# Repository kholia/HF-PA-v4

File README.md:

### HF-PA-v4

VU3CER's Robust `Class-D HF PA` for https://github.com/kholia/Easy-Digital-Beacons-v1
project for 40-20-17-15-10 bands.

For extra fun, use this PA with https://github.com/kholia/HF-Balcony-Antenna-System.

Jan-2022 UPDATE: https://github.com/kholia/HF-PA-v5 is up now.

This design aspires to be the standard mW-to-QRP-Gallon HF PA in the ~600 INR
(8 USD) design space. Well, it does much more than QRP now...

Design Constraints:

- PCB is to be homebrewed.

- PCB is single-sided - only one layer (side) is available for routing.

- IRF510 MOSFET needs to be on an edge to allow usage of heatsinks.

- Typical external linears (e.g. `PA150 HF Linear Amp`) need 2W minimum to
  function. So we need a minimum of 2W of RF output from our design.

- Minimal part count is strongly preferred. Low cost, and ease of availability
  are strong driving and deciding factors.

  The cost of this HF-PA-v4 system is less than one RD16HHF1 MOSFET ;)

- Reproducibility is a MUST! We focus a lot on this aspect by documenting each,
  and every detail possible.

- Repairability in the field is a MUST!

  Dhiru's finding: Repairing homebrewed PCBs is so much easier, and fun than
  reworking commercial `lead-free` PTH PCBs.

- No moving mechanical parts are allowed in the design - this rules out usage
  of (failure-prone) active cooling options like fans.

- We do NOT like the robustness of QCX, QDX, uSDX PAs. Removing heat from TO-92
  devices in a reliable way is not a trivial problem.

Note 0: All screenshots are clickable and zoomable.

Input: Few milliwatts is fine. Note: Si5351's output is around 8-10mW.

Output: With `v4.1` design, we are able to get 12W+ (total power) on the 15m
band with 30% efficiency! With a 5-pole LPF attached, we get ~10W RF output on
the 15m band. Efficiencies and output power levels are much higher on lower
bands! E.g. Power output @ 14 MHz is 14W+ with 51% efficiency - with LPF
attached!

Old results (kept for reference purposes):

Sample output for (14 MHz, 20v, ~725mA IN, 15W DC IN, 5.2W RF OUTPUT, With LPF
attached):

Note 1: The output power is software controllable (via `PWM grounding`) for
flexibility.

Note 2: The idea behind making these (and my other) design notes publicly
available is to deliver REPRODUCIBLE, flexible, home-brewable, standardized,
reasonable, and cost-effective solutions for some common problems. I include
many references, simulations, and notes in my projects to enable you to do your
own (better) designs - do share them ;)

Robustness Notes:

- Ensure that the IRF510 is fastened securely to the heat sink.

  Use lock washers, and thermal epoxy adhesive to ensure good mechanical
  contact.

- We recommend operating at 24v instead of >= 29v.

**Final recommendations from 05-November-2021 (for v4.3)**:

- Using 7805 is recommended instead of 7809 / 7912. Less is more ;)

- Enable `SI5351_DRIVE_8MA` option in code.

- Output results @ 24v:

  - 28.075 MHz (10m): 4W RF OUT (~14.5W DC IN)

  - 21.075 MHz (15m): 5W RF OUT (~13W DC IN)

  - 14.075 MHz (20m): 7W RF OUT (~13W DC IN)

For more power, use 7809 instead of 7805, and remember to take (much) more
care!

Please see the older https://github.com/kholia/HF-PA-v2 project for the
power-supply (over-current protected), and LPF designs.

Schematic:

PCB rendering (v4.1):

Note 3: The HF PA is connected to a 20m dipole over 55 meters of HLF-200 coax.

Note 4: The PCB is done using KiCad - a free, and open EDA software.

Note 5: This PA can be homebrewed from scratch in around 4 to 6 hours (one
afternoon, and an evening).

#### Notes

[From QRP Labs] Si5351A outputs a 3.3v square wave. The power output of Si5351A
is around 8-10mW (10 dBm). The BS170 based driver circuit amplifies this to
~200mW (23 dBm) for a gain of around 13 dB. The IRF510 finals provide a gain of
around 14dB and produce around 5W of RF power.

#### PA tuning process

- Remove the BS170 and IRF510 MOSFETS from their sockets.

- Set DC gate bias for BS170 to 0v. Now increase the bias (via trimpot) until
  the current consumption increases slightly (QRP Labs' process).

  You can also start by setting the gate bias to 2v directly ;)

- For IRF510, set gate bias to 3v. This ensures that IRF510 isn't turned ON -
  double-check this by monitoring the power consumption.

- Connect the MOSFET back, and measure RF output. Happy with the output power? -
  If yes, you are done else follow the next steps.

- Remove the MOSFET, increase the gate bias voltage in very small increments
  (0.1v types).

- Connect the MOSFET back, and measure power consumption without any RF input.
  Ensure that MOSFET remains OFF without any RF input.

- Apply RF input, and measure RF output.

- Repeat these steps as needed.

The [QRP Labs' procedure for bias adjustment](https://www.qrp-labs.com/images/pa/pa_simple_assembly_A4.pdf) and [this document](https://www.qrp-labs.com/images/ultimate3s/assembly_u3s.pdf) seem to have a better description of this process.

#### PA BOM

- 1 x IRF510 (Genuine Vishay parts are tried-and-tested) - 35 to 50 INR

  - The `SEC` (`SEC Electronics Inc`) branded IRF510(s) also work great!

  - The `SEC IRF510` can perform even better than Vishay's version. This
    particular result will vary between different product batches.

  - IRF510 with `International Rectifier` branding are most likely fake or "new
    old stock" if you are very lucky!

    Note: IR and Infineon have stopped manufacturing IRF510 MOSFETs.

  - AliExpress IRF510(s) are likely to be fake

  - The IR IRF510 gave ~3W versus 5.2W+ from SEC IRF510 versus ~5W from
    Vishay's IRF510!

    Note: The gate threshold voltage can vary even between two samples picked
    from the same manufacturer!

  - The Cgs ("gate capacitance") of a fake IRF510 is typically more than 1000pF
    on a LCR-T4 meter. This value is around ~400pF for genuine IRF510 parts on
    a LCR-T4 meter.

  - Ensure proper sourcing (trusted supply chain, etc) to get genuine parts

- BS170 MOSFET - 9 to 15 INR

- 2 x 4.7k Preset (Potentiometer) RM-065 - 12 INR

  - It is easier to get 5k (502) trimpots

- 1 x 3.3k 0.25W MFR - 2 INR

- 1 x 4.7k 0.25W MFR - 2 INR

- 1 x 10 Ohm Resistor 0.25W or 0.5W MFR - 2 INR (MOSFET gate resistor)

- [Optional] 2 x 10k Ohm - 0.25W Metal Film Resistor - 5 INR

- A very large heat sink - 50 to 175 INR - larger heatsink is better!

- 1 x 7805 (TO-220 package from CDIL) Voltage Regulator - 30 INR

  - The ST's 7805 is widely faked - let's avoid it or let's source it properly

- 1 x 1N4001 (or 1N4007) diode for 7805 protection - 2 INR

- 2 x SMA connectors (Vertical PCB mount) - 75 INR

- 1 x 10uF 50v Electrolytic Capacitor - 5 INR

- 8 x 100nF (104) 50v MLCC - 20 INR

- 1 x FT37-43 (Black Toroid, Fair-Rite 5943000201) - less than 25 INR (handles <= 350mW only)

- 1 x FT50-43 (Larger Black Toroid, Fair-Rite 5943000301) - less than 32 INR

- Misc: Relimate Connectors, Copper Clad PCB (Glass Epoxy), Various Consumables
  (~100 INR), SMA cables for testing, RF adapter (SMA Male to SO-239), M3 nuts
  and screws, TO-220 insulator kit

- Tools: LCR-T4 Meter (for measuring things), RF Power Meter

- Optional power supply: LM50-20B24 Mornsun SMPS - 24V 2.2A - 52.8W AC/DC SMPS - 700 INR

- Optional PPTC fuse

- PA Total Cost: Less than 600 INR

#### Power Supply + LPF BOM

See the following projects:

- https://github.com/kholia/HF-PA-v2
- https://github.com/kholia/HF-PA-v3
- 2 x 100 pF (50/100v)
- 1 x 180 pF (50/100v)
- 2 x T50-6 (Yellow Iron Dust code) toroids
- 25 SWG Winding Wire

Note: For LPF, use C0G 100v rated caps!

#### BOM + Equipment Sources

- https://www.semikart.com/ (IRF510, BS170, 100v NP0 LPF caps - Kemet and others)

  - 100v NP0 LPF caps from `Multicomp Pro` brand seem pretty cost-effective

  - 1N5374B 75V 5W Zener Diode (optional - for SWR protection)

- https://www.electronicscomp.com/

  - IRF510, BS170, regular caps, ST voltage regulators

  - Female berg strip (2.54mm pitch)

- https://www.electroncomponents.com/ (transistors, connectors, consumables, misc)

  - https://www.electroncomponents.com/LM7805-5V-Positive-Regulator

  - https://www.electroncomponents.com/BS170-N-channel-Switching-FET

  - https://www.electroncomponents.com/1N4001

  - https://www.electroncomponents.com/mica-insulator-to-220-set-kit

- https://www.sunrom.com/ (regular ceramic caps, SMA connectors)

- https://projectpoint.in/

  - Transistors, regular caps, voltage regulators, pots / trimmers, MFR resistors, misc

  - 2-Pin High Quality Relimate Connectors (all those 2-pin headers are actually Relimate Connectors)

  - Copper Magnetic Winding Wire - 29 SWG and 25 SWG

  - CDIL 7805

  - 3-Pin Relimate Cable Female to Female (High Quality 2500mA) - 'TO-220 socket'

  - 2-Pin Relimate Cable Female (High Quality 2500mA) - for power

  - 2-Pin Relimate Male Header

- Semikart, eBay (`gr_makis`) - Toroids

- https://www.onlinetps.com/shop/ ('IR branded' IRF510 - not recommended!)

- https://www.ktron.in/ (SMA connectors)

- [LCR-T4 LCR Meter](https://www.techtonics.in/lcr-t4-12864-lcd-graphical-transistor-tester-resistance-capacitance-esr-scr-meter)

- https://robu.in/ (voltage boost module)

- See https://github.com/kholia/HF-PA-v2 and https://github.com/kholia/HF-PA-v3 sources too

Note for international buyers: The BOM can be carefully sourced via Mouser and DigiKey.

#### O(Current consumption)

The ESP8266 usually draws a peak current of about 250mA after it wakes up and
then more or less constantly draws around 70mA before it goes back to sleep.

DS3231 -> 5mA

Si5351 -> ~50 to 100mA

PA -> Less than 1 A (rms)

Upper bound -> 1.4A maximum.

#### Tips

MOSFETs are sensitive with regards to ESD and high soldering temperatures. Use
best practices when dealing with MOSFETs and perhaps always ;)

By using these `TO-220 Sockets`, we can easily support any MOSFET pinout. This
technique allows usage of `off-pcb` heat sinks with a lot of flexibility. It
also avoids common ESD + MOSFET problems as well. The gate bias can be easily
checked by safely removing the MOSFET from the TO-220 socket. Also, this socket
idea allows us to safely eliminate the LDO from the design.

A burnt 78(L)05 regulator can easily eat up 4-5W of power by itself. If there
is no RF output but power is being consumed then check your linear regulator.

#### Future ideas

- Use a `PPTC fuse` in the PA voltage line (oscillations can be a real problem,
  and can be nasty) - Sandeep Lohia (VU3SXT).

- Add a `Type K Thermocouple` based temperature monitoring to ensure safety.

- Alternatively, use ACS712 to monitor the current consumption to ensure
  safety.

#### References

See [References.md](./References.md).

#### Credits

This design uses ideas, and support from Hans Summers (G0UPL, QRP Labs), VU3SXT
(Sandeep Lohia), VU2ASH, Mr. Bhatnagar (VU2SPF), AC7LX, and PY2OHH.

Also see https://github.com/kholia/HF-PA-v3#credits and https://github.com/kholia/HF-PA-v2#credits.

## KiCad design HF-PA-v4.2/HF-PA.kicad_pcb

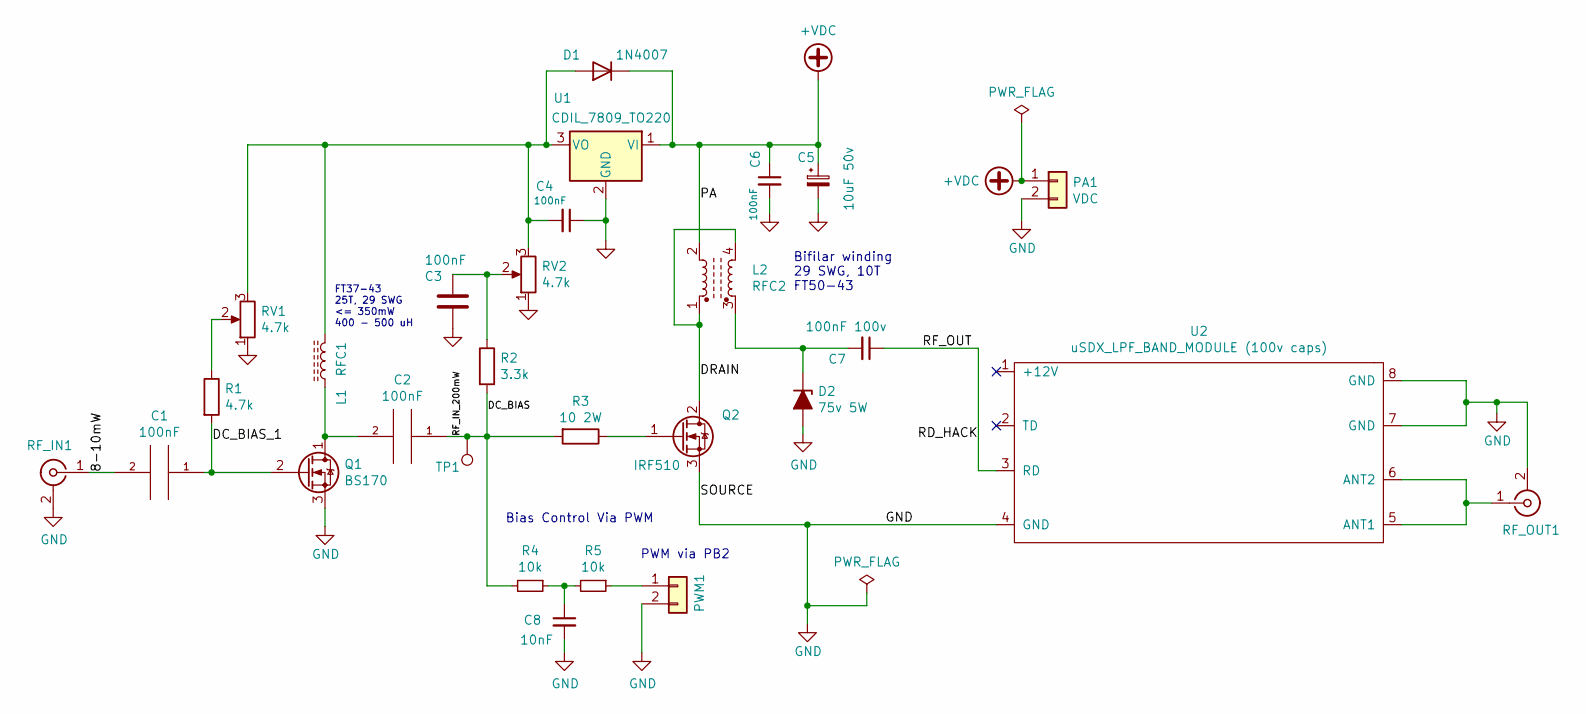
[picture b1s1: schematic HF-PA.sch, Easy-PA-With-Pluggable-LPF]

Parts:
C1, C2, C3, C4, C6: 100nF; C_Disc_D4.3mm_W1.9mm_P5.00mm
C5: 10uF 50v; CP_Radial_D5.0mm_P2.50mm
C7: 100nF 100v; C_Disc_D4.3mm_W1.9mm_P5.00mm
C8: 10nF; C_Disc_D4.3mm_W1.9mm_P5.00mm
D1: 1N4007; D_DO-41_SOD81_P3.81mm_Vertical_AnodeUp
D2: 75v 5W; D_DO-201_P5.08mm_Vertical_AnodeUp
L1: RFC1; L_Toroid_Vertical_L10.0mm_W5.0mm_P5.08mm
L2: RFC2; FT50-43 Transformer
PA1: VDC; PinHeader_1x02_P2.54mm_Vertical
PWM1: Conn_01x02; PinHeader_1x02_P2.54mm_Vertical
Q1: BS170; PinSocket_1x03_P2.54mm_Vertical
Q2: IRF510; TO-220-3_Vertical
R1: 4.7k; R_Axial_DIN0207_L6.3mm_D2.5mm_P2.54mm_Vertical
R2: 3.3k; R_Axial_DIN0207_L6.3mm_D2.5mm_P2.54mm_Vertical
R3: 10 2W; R_Axial_DIN0207_L6.3mm_D2.5mm_P2.54mm_Vertical
R4, R5: 10k; R_Axial_DIN0207_L6.3mm_D2.5mm_P2.54mm_Vertical
RF_IN1: Conn_Coaxial; SMA_Amphenol_901-144_Vertical
RF_OUT1: Conn_Coaxial; SMA_Amphenol_901-144_Vertical
RV1, RV2: 4.7k; Potentiometer_Runtron_RM-065_Vertical
TP1: TestPoint; PinHeader_1x01_P2.54mm_Vertical
U1: CDIL_7809_TO220; TO-220-3_Vertical
U2: uSDX_LPF_BAND_MODULE (100v caps); uSDX_LPF_Band_Module

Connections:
+VDC: C5.1, C6.1, D1.1 (K), L2.2, PA1.1, U1.1 (VI)
/8-10mW: C1.2, RF_IN1.1 (In)
/DC_BIAS: C2.1, R2.2, R3.2, R4.2, TP1.1
/DC_BIAS_1: C1.1, Q1.2 (G), R1.2
/DRAIN: L2.1, L2.4, Q2.2 (D)
/RD_HACK: C7.1, U2.3 (RD)
GND: C3.2, C4.1, C5.2, C6.2, C8.2, D2.2 (A), PA1.2, PWM1.2, Q1.3 (S), Q2.3 (S), RF_IN1.2 (Ext), RF_OUT1.2 (Ext), RV1.1, RV2.1, U1.2 (GND), U2.4 (GND), U2.7 (GND), U2.8 (GND)
unnamed: C2.2, L1.1, Q1.1 (D)
unnamed: C3.1, R2.1, RV2.2
unnamed: C4.2, D1.2 (A), L1.2, RV1.3, RV2.3, U1.3 (VO)
unnamed: C7.2, D2.1 (K), L2.3
unnamed: C8.1, R4.1, R5.2
unnamed: PWM1.1, R5.1
unnamed: Q2.1 (G), R3.1
unnamed: R1.1, RV1.2
unnamed: RF_OUT1.1 (In), U2.5 (ANT1), U2.6 (ANT2)

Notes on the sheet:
Bias Control Via PWM
PWM via PB2
FT37-43 25T, 29 SWG <= 350mW 400 - 500 uH
Bifilar winding 29 SWG, 10T FT50-43

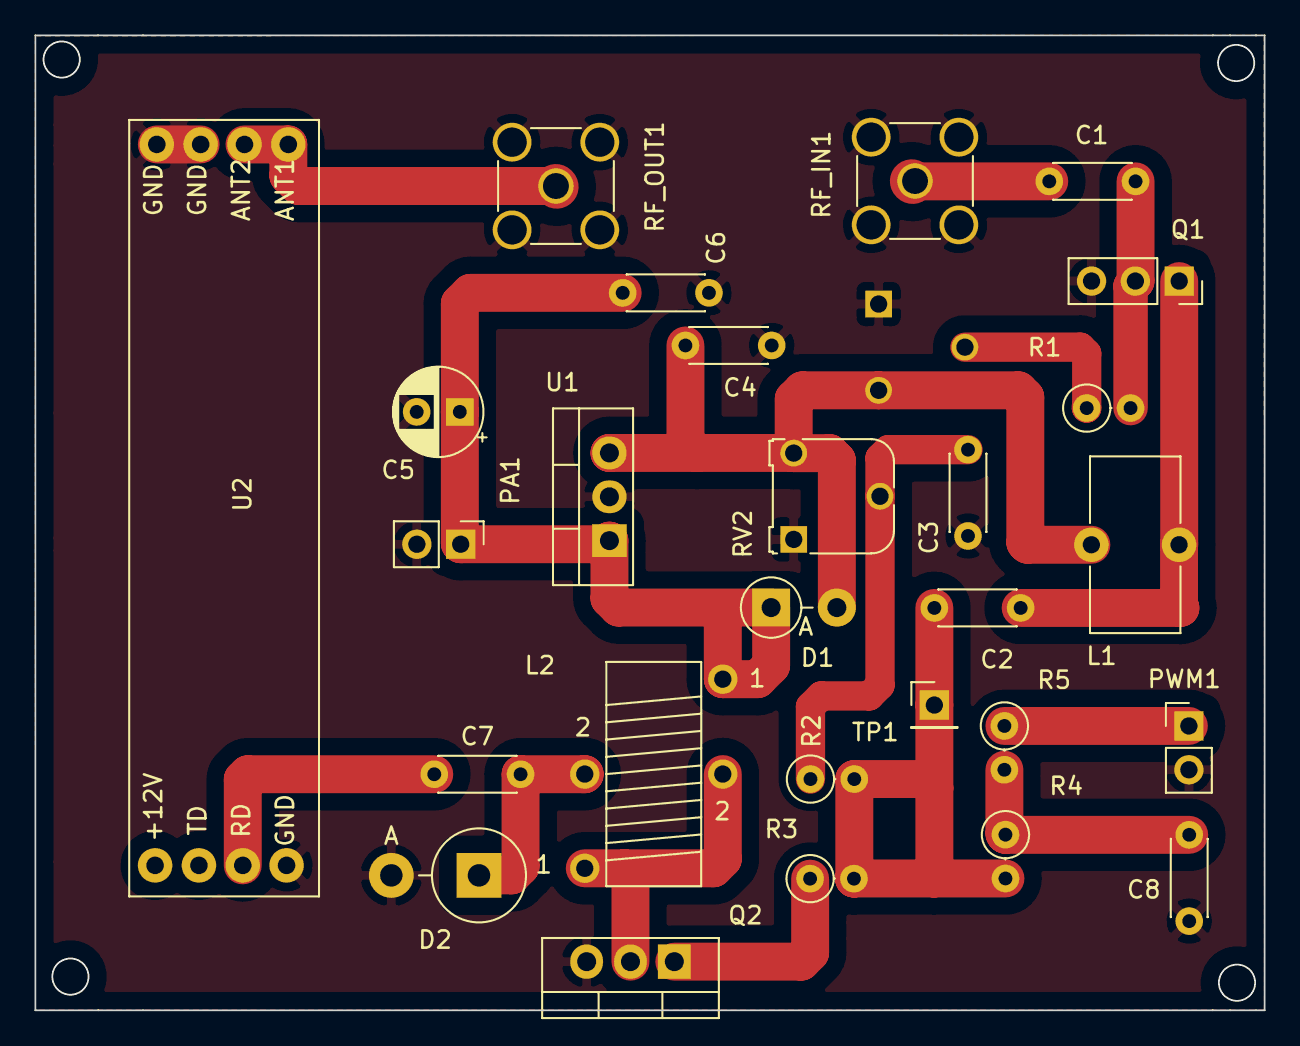
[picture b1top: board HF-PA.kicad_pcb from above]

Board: 2 copper layers, 71.2 x 56.5 mm, 28 parts (1 on the bottom side), 16 nets.
